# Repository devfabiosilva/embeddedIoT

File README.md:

# embeddedIoT
My old project for IoT and automation 8 bit system

## Brief

This is my fisrt and old discontinued home embedded 8bit iot for control, monitoring and automation working 24/7 since 2014 open hardware

## Details

### - Hardware specification

  - Project [folder](/hardware)
  - Last update 2014-04-01

  TODO

### - Firmware specification

  - Project [folder](/firmware_ver1.5)
  - Last update 2015-07-01

### - Uart for IoT using PySerial (Monitoring)

  - Project [folder](/UartForIoT)
  - RS232 protocol using [PySerial](https://pypi.org/project/pyserial/)
  - Script type reads events RS232 -> USB -> TCP
  - Commands using [this reference for reading events](/embeddedsystem.pdf) pages: 32-35
  TODO

## Snapshots

## Specifications

## Export GERBER files

## Installing AVR C (avr-gcc) and compiling firmware

## Upload firmware

## Running Python to read events from RS 232

## License

  - MIT

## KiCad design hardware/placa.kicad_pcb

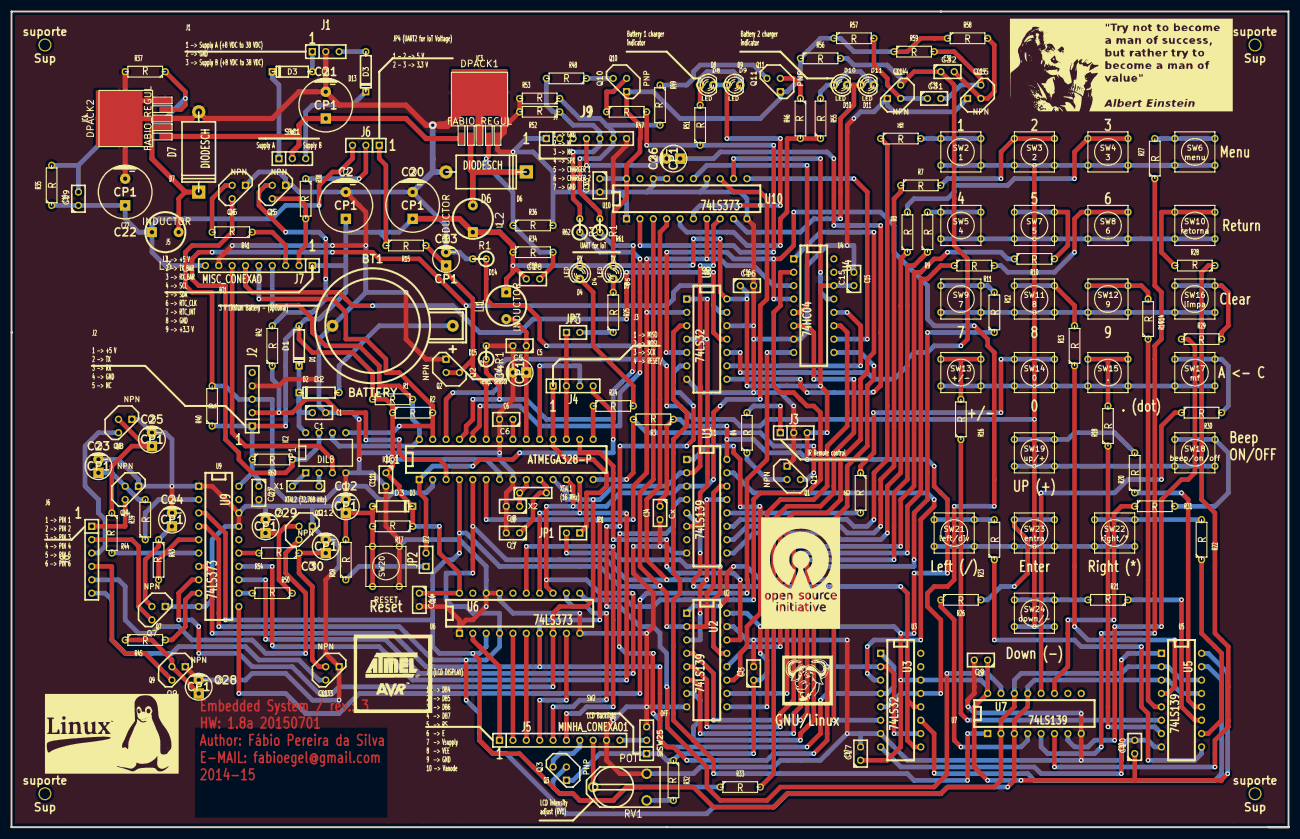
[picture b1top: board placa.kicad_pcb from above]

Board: 2 copper layers, 242.6 x 154.9 mm, 188 parts (0 on the bottom side), 165 nets.

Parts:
BT1: BATTERY; CR2032H
C1, C3, C5, C6, C7, C8, C9, C10, C11, C14, C15, C16, C17, C18, C19, C27, C31, C32, C33: C; C1
C2, C21: CP1; CP_10x16mm
C4, C12, C13, C23, C24, C25, C26, C28, C29, C30: CP1; CP_5x11mm
C20, C22: CP1; CP_10x21mm
Cx: V***; C1
D1, D2, D3: DIODE; D3
D3#2: D12; D3
D3#3: D13; D3
D4, D5, D8, D9, D10, D11: LED; LED-3MM
D6, D7: DIODESCH; D6
DPACK1, DPACK2: FABIO_REGUL; DPAK5
IC1: ATMEGA328-P; DIP-28__300
J1: MINHA_CONEXAO7; SIL-3
J2: MINHA_CONEXAO5; SIL-5
J3: MINHA_CONEXAO6; SIL-3
J4: MINHA_CONEXAO4; SIL-4
J5: MINHA_CONEXAO1; SIL-10
J6: FABIO_CON_3; SIL-3
J7: MISC_CONEXAO; SIL-9
J8: MINHA_CONEXAO2; SIL-6
J9: MINHA_CONEXAO3; SIL-7
JP1, JP2, JP3: JUMPER; SIL-2
L1, L2, L3: INDUCTOR; INDUCTOR_V
P1: DIL8; DIP-8__300
Q1, Q2, Q4, Q5, Q6, Q7, Q8, Q9, Q12, Q13, Q14, Q15: NPN; TO92
Q3, Q10, Q11: PNP; TO92
R1, R2, R3, R4, R5, R6, R7, R8, R9, R10, R11, R12, R13, R14, R15, R16, R17, R18, R19, R20, R21, R22, R23, R24, R25, R26, R27, R28, R29, R30, R31, R32, R33, R34, R35, R36, R37, R38, R39, R40, R41, R42, R43, R44, R45, R46, R47, R48, R49, R50, R51, R52, R53, R54, R55, R56, R57, R58, R59, R60: R; R3
R1#2: R61; R1
R1#3: R62; R1
R1#4: D14; R1
R1#5: D15; R1
RV1: POT; RV2X4
SW1: SWITCH_INV; MICROSWITCH_SPST
SW2: 1; SW_PUSH_SMALL
SW3: 2; SW_PUSH_SMALL
SW4: 3; SW_PUSH_SMALL
SW5: 4; SW_PUSH_SMALL
SW6: menu; SW_PUSH_SMALL
SW7: 5; SW_PUSH_SMALL
SW8: 6; SW_PUSH_SMALL
SW9: 7; SW_PUSH_SMALL
SW10: retorna; SW_PUSH_SMALL
SW11: 8; SW_PUSH_SMALL
SW12: 9; SW_PUSH_SMALL
SW13: +/-; SW_PUSH_SMALL
SW14: 0; SW_PUSH_SMALL
SW15: .; SW_PUSH_SMALL
SW16: limpa; SW_PUSH_SMALL
SW17: mf; SW_PUSH_SMALL
SW18: beep/on/off; SW_PUSH_SMALL
SW19: up/+; SW_PUSH_SMALL
SW20: RESET; SW_PUSH_SMALL
SW21: left/div; SW_PUSH_SMALL
SW22: right/*; SW_PUSH_SMALL
SW23: entra; SW_PUSH_SMALL
SW24: down/-; SW_PUSH_SMALL
SW25: SWITCH_INVe; MICROSWITCH_SPST
U1, U2, U5, U7: 74LS139; DIP-16__300
U3: 74LS32; DIP-16__300
U4: 74HC04; DIP-16__300
U6, U9, U10: 74LS373; DIP-20__300
U8: 74LS32; DIP-14__300
X1, X2: CRYSTAL; C2
suporte: Sup; suporte
suporte#2, suporte#3, suporte#4: Sup; suporte

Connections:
+3.3V: C19.1, C22.1, J6.3, J7.9, L3.1, R35.1
+24V: C21.1, DPACK1.1, DPACK2.1, SW1.2
/00: IC1.4, U1.14, U2.2, U5.2, U5.14, U6.3, U7.2, U7.14, U9.3, U10.3
/01: IC1.5, U1.13, U2.3, U5.3, U5.13, U6.4, U7.3, U7.13, U9.4, U10.4
/02: IC1.6, U3.2, U3.10, U4.3, U6.7, U8.2, U9.7, U10.7
/03: IC1.11, U1.2, U6.8, U9.8, U10.8
/04: IC1.12, U1.3, U6.13, U9.13, U10.13
/05: IC1.13, U6.14, U9.14
/a1: IC1.24, R1#3.1, R1#4.1
/a2: IC1.25, R1#2.1, R1#5.1
GND: BT1.2, C1.2, C2.2, C3.2, C4.2, C5.2, C6.2, C7.2, C8.2, C9.2, C10.2, C11.2, C12.2, C13.2, C14.2, C15.2, C16.2, C17.2, C20.2, C21.2, C22.2, C23.2, C24.2, C25.2, C27.2, C28.2, C29.2, C30.2, C33.2, Cx.2, D6.1, D7.1, DPACK1.3, DPACK1.5, DPACK2.3, DPACK2.5, IC1.8, IC1.22, J1.2, J2.4, J3.2, J5.9, J7.8, J9.1, J9.7, P1.4, Q1.1, Q2.1, Q4.1, Q5.1, Q6.1, Q7.1, Q8.1, Q9.1, Q12.1, Q13.1, Q14.1, Q15.1, R1#4.2, R1#5.2, R36.2, R37.2, R52.2, R53.2, RV1.3, SW20.2, SW25.3, U1.8, U2.8, U2.15, U3.7, U4.7, U5.8, U6.1, U6.10, U6.17, U6.18, U7.8, U8.7, U8.12, U9.1, U9.10, U9.17, U9.18, U10.1, U10.10, U10.14, U10.17, U10.18
unnamed: P1.1, X1.2
unnamed: P1.2, X1.1
unnamed: J8.2, Q7.3
unnamed: D8.1, D9.2, R51.2
unnamed: D8.2, D9.1, U10.6
unnamed: D10.1, D11.2, R55.2
unnamed: R47.2, R51.1, U10.2
unnamed: C26.2, J9.4
unnamed: C26.1, U8.8
unnamed: BT1.1, D2.1
unnamed: Q1.2, R4.1
unnamed: J3.1, R4.2
unnamed: D3#3.2, SW1.3
unnamed: D3#2.2, SW1.1
unnamed: R54.2, U9.15
unnamed: J8.1, Q4.3
unnamed: J8.4, Q9.3
unnamed: J8.6, Q13.3
unnamed: R39.1, U9.2
unnamed: R43.2, U9.5
unnamed: Q3.2, R33.1
unnamed: Q10.3, R48.1
unnamed: Q11.3, R49.1
unnamed: Q10.2, R47.1
unnamed: Q11.2, R46.1
unnamed: J8.5, Q12.3
unnamed: J8.3, Q8.3
unnamed: C32.2, Q15.2, R58.2
unnamed: J5.10, SW25.2
unnamed: J5.8, RV1.2
unnamed: J5.7, Q3.3
unnamed: C24.1, Q7.2, R43.1
unnamed: D4.2, R24.2
unnamed: D5.2, R25.2
unnamed: J6.2, R38.1
unnamed: IC1.14, Q1.3, R3.2
unnamed: J7.3, R41.1
unnamed: C23.1, Q4.2, R39.2
unnamed: C25.1, Q8.2, R44.1
unnamed: C28.1, Q9.2, R45.1
unnamed: C29.1, Q12.2, R50.1
unnamed: C30.1, Q13.2, R54.1
unnamed: C18.2, DPACK1.4, R34.2, R36.1
unnamed: D6.2, DPACK1.2, L2.2
unnamed: J7.2, Q5.3, R38.2
unnamed: Q6.2, R41.2
unnamed: Q5.2, R42.2
unnamed: JP3.2, R25.1
unnamed: R8.2, SW4.1
unnamed: R10.2, SW7.1
unnamed: R14.2, SW12.1
unnamed: R5.1, SW14.1
unnamed: R20.2, SW19.1
unnamed: R23.2, SW21.1
unnamed: R22.2, SW22.1
unnamed: R26.2, SW23.1
unnamed: U3.8, U5.1
unnamed: U3.11, U5.15
unnamed: IC1.1, J4.4, JP2.2
unnamed: JP2.1, R19.1
unnamed: R6.2, SW2.1
unnamed: R7.2, SW3.1
unnamed: R28.2, SW10.1
unnamed: R30.2, SW17.1
unnamed: R9.2, SW5.1
unnamed: R12.2, SW9.1
unnamed: R16.2, SW13.1
unnamed: U1.1, U2.11
unnamed: U2.10, U4.9
unnamed: U2.9, U4.11
unnamed: C6.1, IC1.21
unnamed: IC1.19, J4.3
unnamed: IC1.16, U2.14
unnamed: C13.1, IC1.23, Q2.2, Q2.3, R15.2
unnamed: JP1.2, U2.13
unnamed: R5.2, U1.12
unnamed: R6.1, U1.11
unnamed: R7.1, U1.10
unnamed: R8.1, U1.9
unnamed: R9.1, U2.4
unnamed: C8.1, IC1.9, X2.1
unnamed: U4.2, U6.11
unnamed: J5.4, U6.9
unnamed: J5.3, U6.6
unnamed: J5.2, U6.5
unnamed: J5.1, U6.2
unnamed: U1.6, U8.1, U8.4
unnamed: U7.15, U8.6
unnamed: C32.1, Q14.3, R56.2, U8.10
unnamed: J5.6, U6.15
unnamed: J5.5, U6.12
unnamed: D10.2, D11.1, U10.9
unnamed: R32.2, RV1.1
unnamed: R50.2, U9.12
unnamed: U4.8, U9.11
unnamed: R44.2, U9.6
unnamed: R26.1, U7.4
unnamed: U1.15, U3.3
unnamed: U2.1, U3.6
unnamed: R12.1, U2.7
unnamed: R11.2, SW8.1
unnamed: R11.1, U2.6
unnamed: R10.1, U2.5
unnamed: R16.1, U5.6
unnamed: R13.2, SW11.1
unnamed: R13.1, U5.4
unnamed: R18.1, U5.7
unnamed: R14.1, U5.5
unnamed: R22.1, U5.10
unnamed: R20.1, U5.12
unnamed: R23.1, U5.9
unnamed: R21.2, SW24.1
unnamed: R21.1, U5.11
unnamed: R29.2, SW16.1
unnamed: R29.1, U7.7
unnamed: R28.1, U7.6
unnamed: R31.2, SW18.1
unnamed: R31.1, U7.11
unnamed: R30.1, U7.12
unnamed: R27.2, SW6.1
unnamed: R27.1, U7.5
unnamed: R33.2, U4.6
unnamed: U4.5, U10.15
unnamed: U4.13, U10.12
unnamed: U4.12, U8.9
unnamed: U1.5, U3.9, U3.12
unnamed: U2.12, U4.1
unnamed: U4.10, U10.11
unnamed: C12.1, D3.1, R17.2, R19.2, SW20.1
unnamed: R18.2, SW15.1
unnamed: U7.1, U8.3
unnamed: U1.4, U3.1, U3.4
unnamed: R45.2, U9.9
unnamed: C19.2, DPACK2.4, R35.2, R37.1
unnamed: D7.2, DPACK2.2, L3.2
unnamed: C1.1, D1.2, D2.2, P1.8
unnamed: C31.2, Q15.3, R59.2
unnamed: C31.1, Q14.2, R57.2
unnamed: IC1.18, J4.1, JP1.1
unnamed: R46.2, R55.1, U10.5
unnamed: C4.1, C5.1, IC1.20, L1.2
unnamed: C7.1, IC1.10, X2.2
unnamed: U3.5, U3.13, U4.4, U8.5
unnamed: IC1.26, SW2.2, SW3.2, SW4.2, SW5.2, SW6.2, SW7.2, SW8.2, SW9.2, SW10.2, SW11.2, SW12.2, SW13.2, SW14.2, SW15.2, SW16.2, SW17.2, SW18.2, SW19.2, SW21.2, SW22.2, SW23.2, SW24.2
RTC_CLK: J7.6, U8.11
RTC_CLK_OPEN_DRAIN: P1.7, R60.2, U8.13
RTC_INT_OPEN_DRAIN: J7.7, P1.3
RX: IC1.2, J2.3, Q6.3, R40.2
SCL: IC1.28, J7.4, P1.6, R1.2
SDA: IC1.27, J7.5, P1.5, R2.2
TO_LED_RX: IC1.15, R24.1
TO_LED_TX: IC1.17, J4.2, JP3.1
TX: IC1.3, J2.2, R42.1
VCC: C2.1, C3.1, C9.1, C10.1, C11.1, C14.1, C15.1, C16.1, C17.1, C18.1, C20.1, C27.1, C33.1, Cx.1, D1.1, D3.2, D4.1, D5.1, IC1.7, J2.1, J3.3, J6.1, J7.1, L1.1, L2.1, Q3.1, Q10.1, Q11.1, R1.1, R2.1, R3.1, R15.1, R17.1, R32.1, R34.1, R40.1, R56.1, R57.1, R58.1, R59.1, R60.1, SW25.1, U1.16, U2.16, U3.14, U4.14, U5.16, U6.20, U7.16, U8.14, U9.20, U10.20

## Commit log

2021-08-16 Adding old documentation
2021-08-18 Add low frequency feature
2021-08-19 Adding firmware and hardware
2021-08-19 Adding some snapshot
2021-08-19 Updating ReadMe
2021-08-19 Correcting firmware path
2021-11-02 Adding RTC clock

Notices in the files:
hardware/placa.kicad_pcb:
(c) 2015 All rights reserved
